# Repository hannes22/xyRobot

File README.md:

# xyRobot

xyRobot is the Framework for my Robot. [Visit my website for more informations](http://xythobuz.org/index.php?p=rob).

## Software used

 + [Peter Fleurys TWI Library](http://homepage.hispeed.ch/peterfleury/avr-software.html)
 + [Linux Version of Peter Danneggers 'fastboot' by H. C. Zimmerer](http://www.mikrocontroller.net/topic/146638)
 + [A Linux compatible Upload Software for fastboot](http://www.avrfreaks.net/index.php?module=Freaks%20Academy&func=viewItem&item_type=project&item_id=1927)

## xyRobotRemote

xyRobotRemote is a Java App which communicates with the Robot Firmware over a serial port. It allows you to shoot pictures with the Gameboy camera and remote-control the robot. It requires Java 6 and could possibly work with Java 7...

## Protocol

The protocol used by the xyRobot Firmware and xyRobotRemote to remote-control the robot is as follows.

<table>
<tr><th>Character Sequence</th><th>Action</th></tr>
<tr><td>ASCII '?'</td><td>Print Firmware Version String</td></tr>
<tr><td>0x80, x</td><td>Rotate the camera Up/Down to the position indicated by the next byte, x, (0 to 180)</td></tr>
<tr><td>0x81, x</td><td>Same as 0x80, but Left/Right</td></tr>
<tr><td>0x82, r1...r8</td><td>Send picture. Camera Register Settings set with the following 8 bytes.</td></tr>
<tr><td>0x83, d, s, dir</td><td>Drive dist cm with speed speed. Direction Forwards if dir = 1, Backwards if dir = 0</td></tr>
<tr><td>0x84, deg, dir</td><td>Rotate deg Degree. Direction Right if dir = 1, ;eft if dir = 0</td></tr>
<tr><td>0x85, r1...r8</td><td>Send picture with 4bit per Pixel.</td></tr>
<tr><td>0x86</td><td>Returns measured distance.</td></tr>
<tr><td>0x87, r1...r8</td><td>Send picture with 2bit per Pixel.</td></tr>
<tr><td>0x88, r1...r8</td><td>Send picture with 1bit per Pixel.</td></tr>
</table>

New major releases could change this protocol or make additions.

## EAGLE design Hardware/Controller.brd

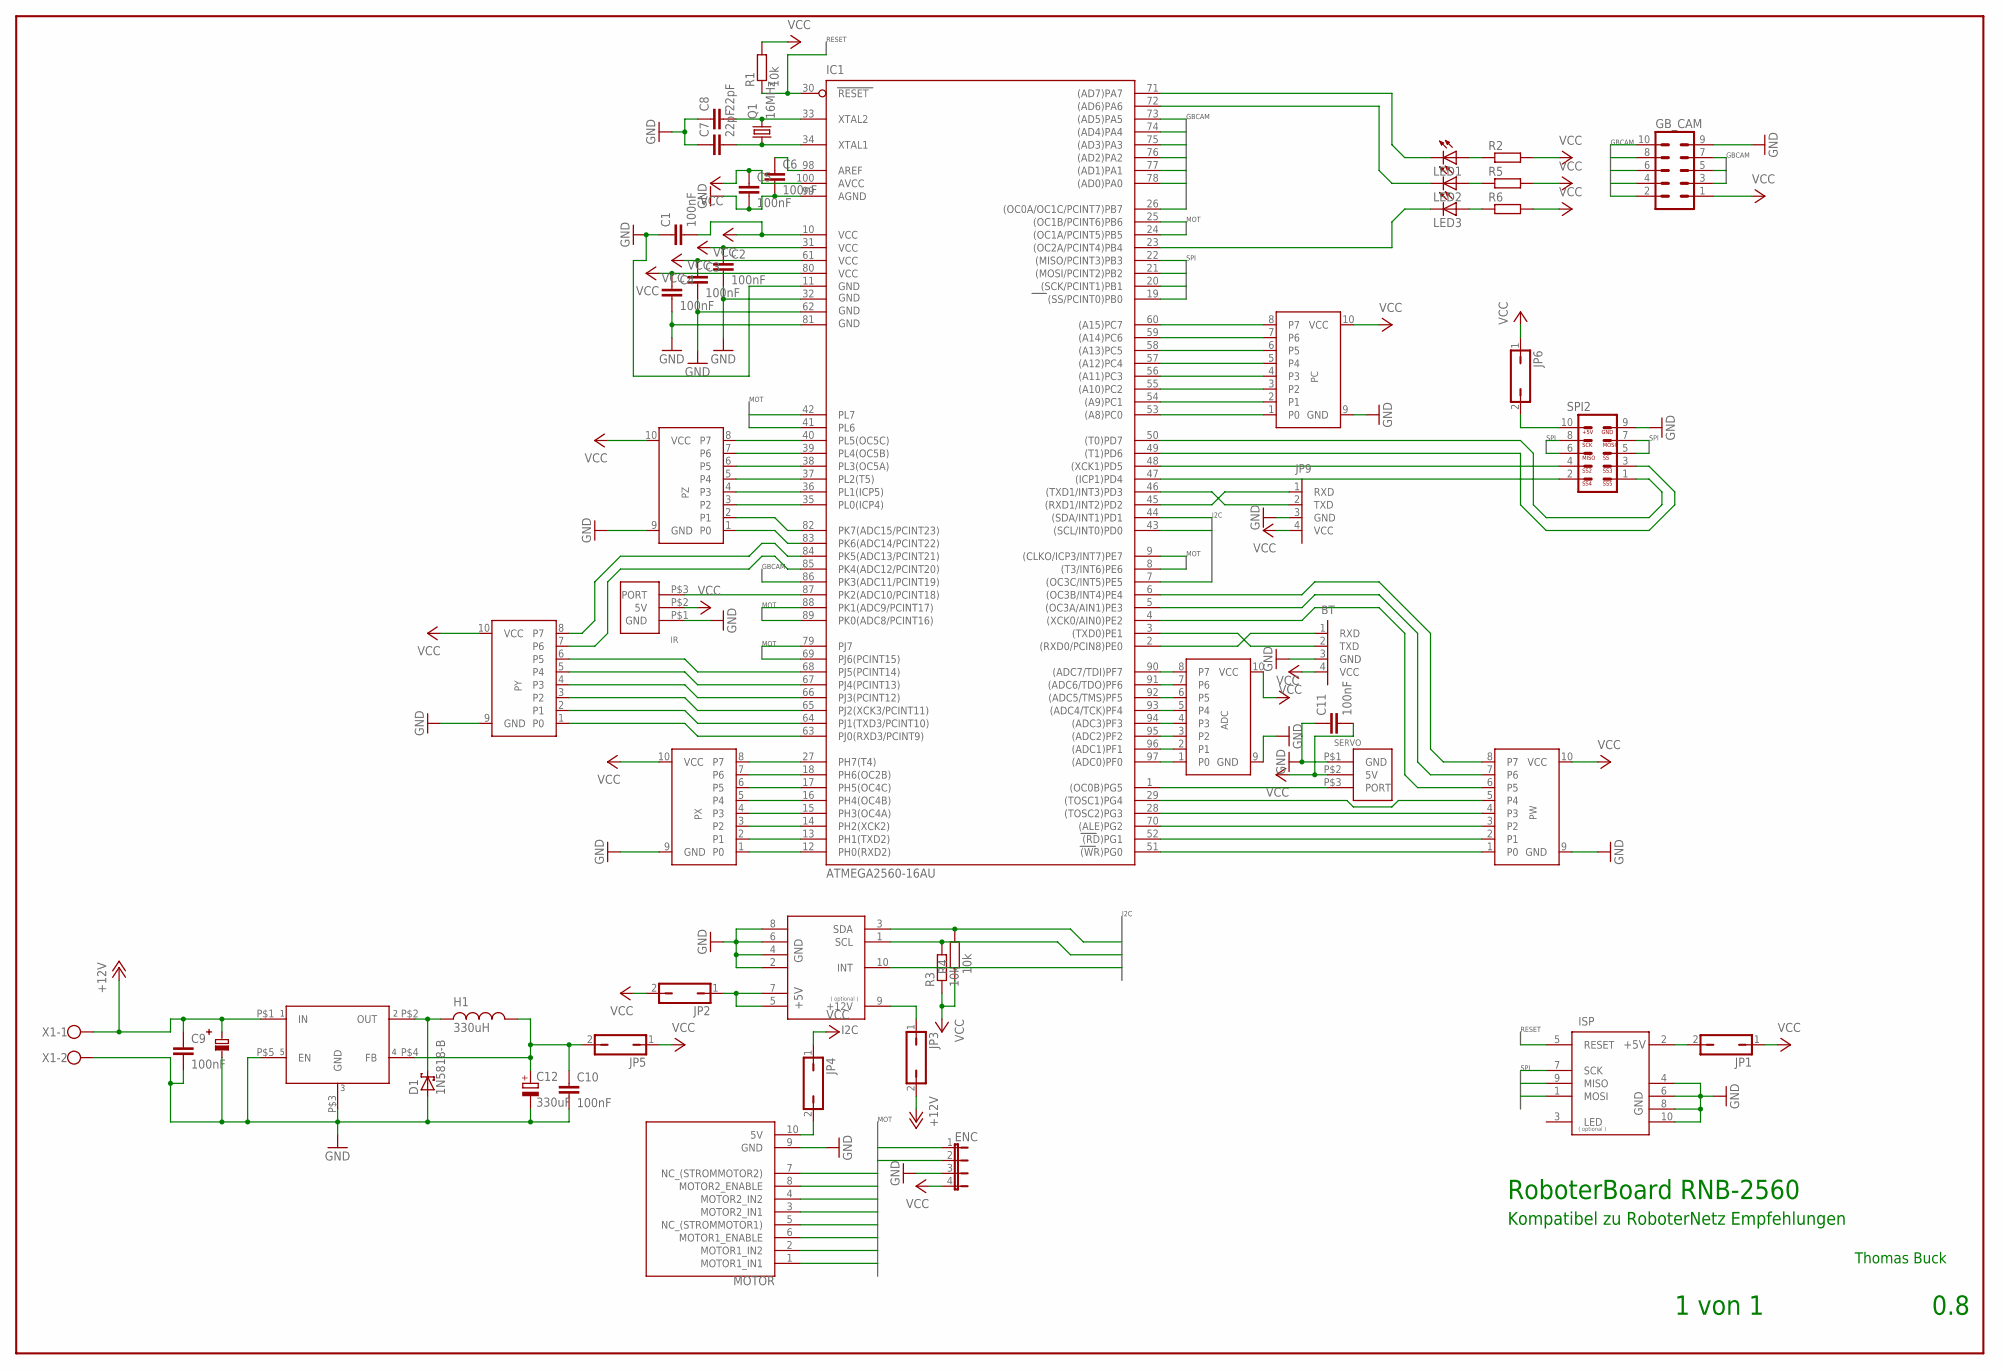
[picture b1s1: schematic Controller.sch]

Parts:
ADC: PORT; ML10
BT: RS232_TTL; 1X04
C1, C2, C3, C4, C5, C6, C9, C10, C11: 100nF; C0603
C7, C8: 22pF; C0603
C12: 330uF; PANASONIC_F
D1: 1N5818-B; DO41-7.6
ENC: JP4E; JP4
GB_CAM: ML10
H1: 330uH; PISR
I2C: I2C; ML10
IC1: ATMEGA2560-16AU; TQFP100
IR: UNIPORT3POL; 1X3SERVO
ISP: AVR-ISP; ML10
JP1, JP2, JP3, JP4, JP5, JP6: JP1Q; JP1
JP9: RS232_TTL; 1X04
LED1, LED2, LED3: LEDCHIP-LED0603; CHIP-LED0603
LM2576-5: LM2576; TO-220
MOTOR: MOTORSTTCKER10POLRNNORM; ML10
PC: PORT; ML10
PW: PORT; ML10
PX: PORT; ML10
PY: PORT; ML10
PZ: PORT; ML10
Q1: 16MHz; HC49/S
R1, R3, R4: 10k; R0603
R2, R5, R6: R-EU_R0603; R0603
SERVO: UNIPORT3POL; 1X3SERVO
SPI2: SPISTECKER; ML10
U$1: 100uF; ELKO_SMD_6.5
X1: W237-102

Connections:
+12V: C9.1, JP3.2, LM2576-5.P$1 (IN), U$1.P$2, X1.1
ANALOG: GB_CAM.8, IC1.86 (PK3(ADC11/PCINT19))
CLK: GB_CAM.6, IC1.77 ((AD1)PA1)
DATA: GB_CAM.3, IC1.74 ((AD4)PA4)
DATASET: GB_CAM.4, IC1.75 ((AD3)PA3)
DREHL: ENC.1, IC1.9 ((CLKO/ICP3/INT7)PE7)
DREHR: ENC.2, IC1.8 ((T3/INT6)PE6)
GND: ADC.9 (GND), BT.3 (GND), C1.1, C2.2, C3.2, C4.2, C5.2, C6.2, C7.1, C8.1, C9.2, C10.2, C11.1, C12.-, D1.A, ENC.3, GB_CAM.9, I2C.2 (GND), I2C.4 (GND), I2C.6 (GND), I2C.8 (GND), IC1.11 (GND), IC1.32 (GND1), IC1.62 (GND2), IC1.81 (GND3), IC1.99 (AGND), IR.P$1 (GND), ISP.4 (GND), ISP.6 (GND), ISP.8 (GND), ISP.10 (GND), JP9.3 (GND), LM2576-5.P$3 (GND), LM2576-5.P$5 (EN), MOTOR.9 (GND), PC.9 (GND), PW.9 (GND), PX.9 (GND), PY.9 (GND), PZ.9 (GND), SERVO.P$1 (GND), SPI2.9, U$1.P$1, X1.2
IN1L: IC1.42 (PL7), MOTOR.1 (MOTOR1_IN1)
IN1R: IC1.79 (PJ7), MOTOR.3 (MOTOR2_IN1)
IN2L: IC1.41 (PL6), MOTOR.2 (MOTOR1_IN2)
IN2R: IC1.69 (PJ6(PCINT15)), MOTOR.4 (MOTOR2_IN2)
INT: I2C.10 (INT), IC1.7 ((OC3C/INT5)PE5)
MISO: IC1.22 ((MISO/PCINT3)PB3), ISP.9 (MISO), SPI2.6
MOSI: IC1.21 ((MOSI/PCINT2)PB2), ISP.1 (MOSI), SPI2.7
unnamed: IC1.87 (PK2(ADC10/PCINT18)), IR.P$3 (PORT)
unnamed: C6.1, IC1.98 (AREF)
unnamed: C8.2, IC1.33 (XTAL2), Q1.2
unnamed: C7.2, IC1.34 (XTAL1), Q1.1
unnamed: IC1.1 ((OC0B)PG5), SERVO.P$3 (PORT)
unnamed: IC1.60 ((A15)PC7), PC.8 (P7)
unnamed: IC1.59 ((A14)PC6), PC.7 (P6)
unnamed: IC1.58 ((A13)PC5), PC.6 (P5)
unnamed: IC1.57 ((A12)PC4), PC.5 (P4)
unnamed: IC1.56 ((A11)PC3), PC.4 (P3)
unnamed: IC1.55 ((A10)PC2), PC.3 (P2)
unnamed: IC1.54 ((A9)PC1), PC.2 (P1)
unnamed: IC1.53 ((A8)PC0), PC.1 (P0)
unnamed: IC1.12 (PH0(RXD2)), PX.1 (P0)
unnamed: IC1.13 (PH1(TXD2)), PX.2 (P1)
unnamed: IC1.14 (PH2(XCK2)), PX.3 (P2)
unnamed: IC1.15 (PH3(OC4A)), PX.4 (P3)
unnamed: IC1.16 (PH4(OC4B)), PX.5 (P4)
unnamed: IC1.17 (PH5(OC4C)), PX.6 (P5)
unnamed: IC1.18 (PH6(OC2B)), PX.7 (P6)
unnamed: IC1.27 (PH7(T4)), PX.8 (P7)
unnamed: IC1.40 (PL5(OC5C)), PZ.8 (P7)
unnamed: IC1.39 (PL4(OC5B)), PZ.7 (P6)
unnamed: IC1.38 (PL3(OC5A)), PZ.6 (P5)
unnamed: IC1.37 (PL2(T5)), PZ.5 (P4)
unnamed: IC1.36 (PL1(ICP5)), PZ.4 (P3)
unnamed: IC1.35 (PL0(ICP4)), PZ.3 (P2)
unnamed: IC1.82 (PK7(ADC15/PCINT23)), PZ.2 (P1)
unnamed: IC1.83 (PK6(ADC14/PCINT22)), PZ.1 (P0)
unnamed: IC1.63 (PJ0(RXD3/PCINT9)), PY.1 (P0)
unnamed: IC1.64 (PJ1(TXD3/PCINT10)), PY.2 (P1)
unnamed: IC1.65 (PJ2(XCK3/PCINT11)), PY.3 (P2)
unnamed: IC1.66 (PJ3(PCINT12)), PY.4 (P3)
unnamed: IC1.67 (PJ4(PCINT13)), PY.5 (P4)
unnamed: IC1.68 (PJ5(PCINT14)), PY.6 (P5)
unnamed: IC1.85 (PK4(ADC12/PCINT20)), PY.7 (P6)
unnamed: IC1.84 (PK5(ADC13/PCINT21)), PY.8 (P7)
unnamed: IC1.51 ((WR)PG0), PW.1 (P0)
unnamed: IC1.52 ((RD)PG1), PW.2 (P1)
unnamed: IC1.70 ((ALE)PG2), PW.3 (P2)
unnamed: IC1.28 ((TOSC2)PG3), PW.4 (P3)
unnamed: IC1.29 ((TOSC1)PG4), PW.5 (P4)
unnamed: IC1.4 ((XCK0/AIN0)PE2), PW.6 (P5)
unnamed: IC1.5 ((OC3A/AIN1)PE3), PW.7 (P6)
unnamed: IC1.6 ((OC3B/INT4)PE4), PW.8 (P7)
unnamed: JP6.2, SPI2.10
unnamed: IC1.47 ((ICP1)PD4), SPI2.2
unnamed: IC1.48 ((XCK1)PD5), SPI2.4
unnamed: IC1.50 ((T0)PD7), SPI2.1
unnamed: IC1.23 ((OC2A/PCINT4)PB4), LED3.C
unnamed: IC1.72 ((AD6)PA6), LED2.C
unnamed: IC1.71 ((AD7)PA7), LED1.C
unnamed: IC1.49 ((T1)PD6), SPI2.3
unnamed: ISP.2 (+5V), JP1.2
unnamed: I2C.5 (+5V), I2C.7 (+5V), JP2.1
unnamed: I2C.9 (+12V), JP3.1
unnamed: JP4.2, MOTOR.10 (5V)
unnamed: ADC.8 (P7), IC1.90 ((ADC7/TDI)PF7)
unnamed: LED1.A, R2.1
unnamed: LED2.A, R5.1
unnamed: LED3.A, R6.1
unnamed: ADC.7 (P6), IC1.91 ((ADC6/TDO)PF6)
unnamed: ADC.6 (P5), IC1.92 ((ADC5/TMS)PF5)
unnamed: D1.C, H1.P$1, LM2576-5.P$2 (OUT)
unnamed: ADC.5 (P4), IC1.93 ((ADC4/TCK)PF4)
unnamed: ADC.4 (P3), IC1.94 ((ADC3)PF3)
unnamed: ADC.3 (P2), IC1.95 ((ADC2)PF2)
unnamed: ADC.2 (P1), IC1.96 ((ADC1)PF1)
unnamed: ADC.1 (P0), IC1.97 ((ADC0)PF0)
unnamed: IC1.46 ((TXD1/INT3)PD3), JP9.2 (TXD)
unnamed: IC1.45 ((RXD1/INT2)PD2), JP9.1 (RXD)
unnamed: C10.1, C12.+, H1.P$2, JP5.2, LM2576-5.P$4 (FB)
PWML: IC1.25 ((OC1B/PCINT6)PB6), MOTOR.6 (MOTOR1_ENABLE)
PWMR: IC1.24 ((OC1A/PCINT5)PB5), MOTOR.8 (MOTOR2_ENABLE)
READIMG: GB_CAM.7, IC1.78 ((AD0)PA0)
RESET: IC1.30 (RESET), ISP.5 (RESET), R1.1
RX: BT.1 (RXD), IC1.2 ((RXD0/PCIN8)PE0)
SCK: IC1.20 ((SCK/PCINT1)PB1), ISP.7 (SCK), SPI2.8
SCL: I2C.1 (SCL), IC1.43 ((SCL/INT0)PD0), R3.2
SDA: I2C.3 (SDA), IC1.44 ((SDA/INT1)PD1), R4.2
SENSL: IC1.88 (PK1(ADC9/PCINT17)), MOTOR.5 (NC_(STROMMOTOR1))
SENSR: IC1.89 (PK0(ADC8/PCINT16)), MOTOR.7 (NC_(STROMMOTOR2))
SERVO: GB_CAM.10, IC1.26 ((OC0A/OC1C/PCINT7)PB7)
SS: IC1.19 ((SS/PCINT0)PB0), SPI2.5
START: GB_CAM.2, IC1.73 ((AD5)PA5)
SYSRES: GB_CAM.5, IC1.76 ((AD2)PA2)
TX: BT.2 (TXD), IC1.3 ((TXD0)PE1)
VCC: ADC.10 (VCC), BT.4 (VCC), C1.2, C2.1, C3.1, C4.1, C5.1, C11.2, ENC.4, GB_CAM.1, IC1.10 (VCC), IC1.31 (VCC1), IC1.61 (VCC2), IC1.80 (VCC3), IC1.100 (AVCC), IR.P$2 (5V), JP1.1, JP2.2, JP4.1, JP5.1, JP6.1, JP9.4 (VCC), PC.10 (VCC), PW.10 (VCC), PX.10 (VCC), PY.10 (VCC), PZ.10 (VCC), R1.2, R2.2, R3.1, R4.1, R5.2, R6.2, SERVO.P$2 (5V)

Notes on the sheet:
RoboterBoard RNB-2560
Thomas Buck
Kompatibel zu RoboterNetz Empfehlungen
0.8
MOT
I2C
SPI
RESET
GBCAM
1 von 1

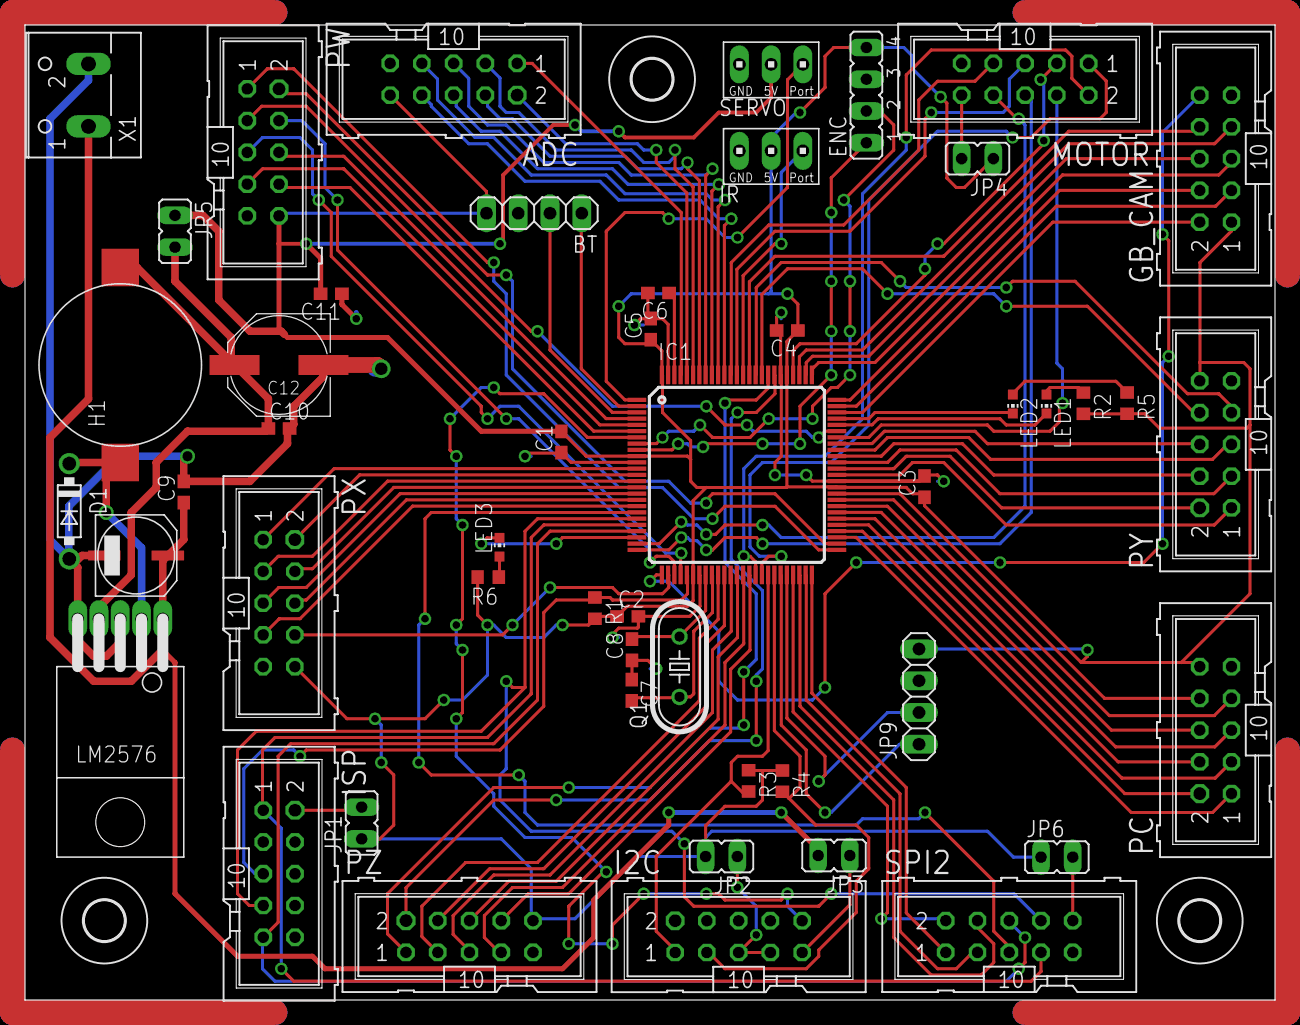
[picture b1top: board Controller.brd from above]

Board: 2 copper layers, 100.0 x 78.0 mm, 53 parts (0 on the bottom side), 103 nets.

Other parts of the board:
U$2, U$3, U$4: 3,2

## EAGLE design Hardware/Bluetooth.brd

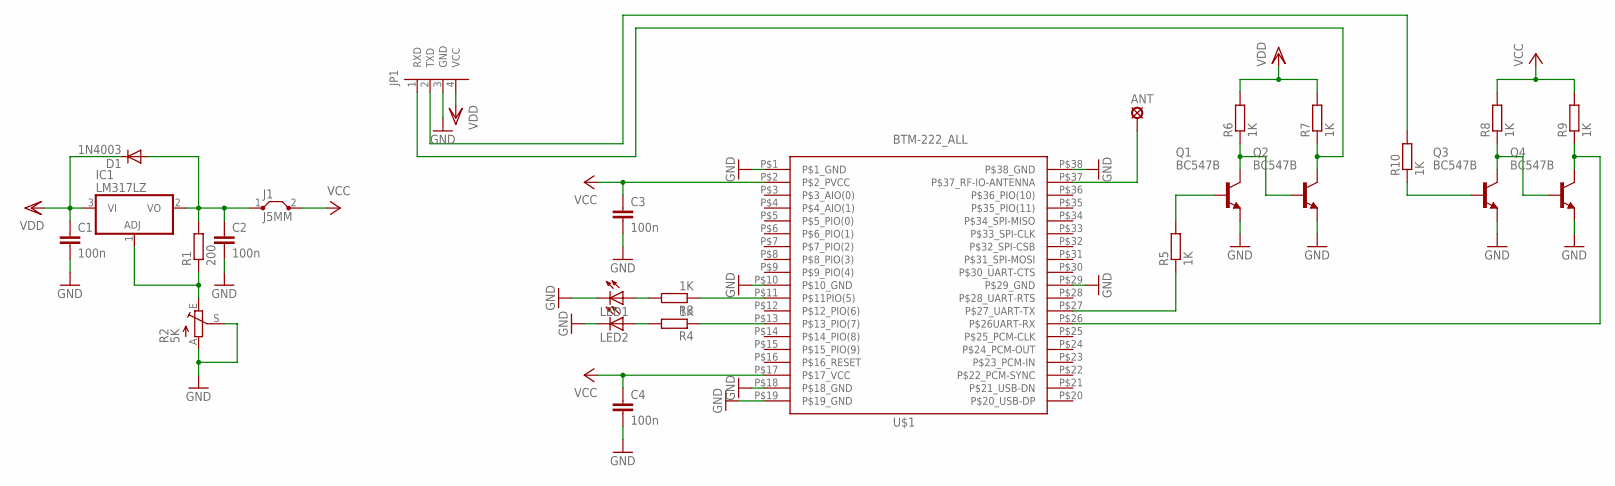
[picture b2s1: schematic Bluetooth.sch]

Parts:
ANT: SE14
C1, C2, C3, C4: 100n; C050-030X075
D1: 1N4003; DO41-10
IC1: LM317LZ; TO92
J1: J5MM; 05
JP1: RS232_TTL; 1X04
LED1, LED2: LED3MM
Q1, Q2, Q3, Q4: BC547B; TO92
R1: 200; 0207/10
R2: 5K; PT-10S
R3, R4, R5, R6, R7, R8, R9, R10: 1K; 0207/10
U$1: BTM-222_ALL; BTM-222

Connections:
GND: C1.2, C2.2, C3.2, C4.2, JP1.3 (GND), LED1.K (C), LED2.K (C), Q1.1 (E), Q2.1 (E), Q3.1 (E), Q4.1 (E), R2.A, R2.S, U$1.P$1 (P$1_GND), U$1.P$10 (P$10_GND), U$1.P$18 (P$18_GND), U$1.P$19 (P$19_GND), U$1.P$29 (P$29_GND), U$1.P$38 (P$38_GND)
unnamed: R3.1, U$1.P$11 (P$11PIO(5))
unnamed: LED1.A, R3.2
unnamed: IC1.1 (ADJ), R1.1, R2.E
unnamed: R4.1, U$1.P$13 (P$13_PIO(7))
unnamed: LED2.A, R4.2
unnamed: Q1.2 (B), R5.2
unnamed: JP1.1 (RXD), Q2.3 (C), R7.1
unnamed: Q1.3 (C), Q2.2 (B), R6.1
unnamed: JP1.2 (TXD), R10.2
unnamed: Q3.2 (B), R10.1
unnamed: R5.1, U$1.P$27 (P$27_UART-TX)
unnamed: Q3.3 (C), Q4.2 (B), R8.1
unnamed: Q4.3 (C), R9.1, U$1.P$26 (P$26UART-RX)
unnamed: ANT.MP, U$1.P$37 (P$37_RF-IO-ANTENNA)
unnamed: C2.1, D1.A, IC1.2 (VO), J1.1, R1.2
VCC: C3.1, C4.1, J1.2, R8.2, R9.2, U$1.P$2 (P$2_PVCC), U$1.P$17 (P$17_VCC)
VDD: C1.1, D1.C, IC1.3 (VI), JP1.4 (VCC), R6.2, R7.2

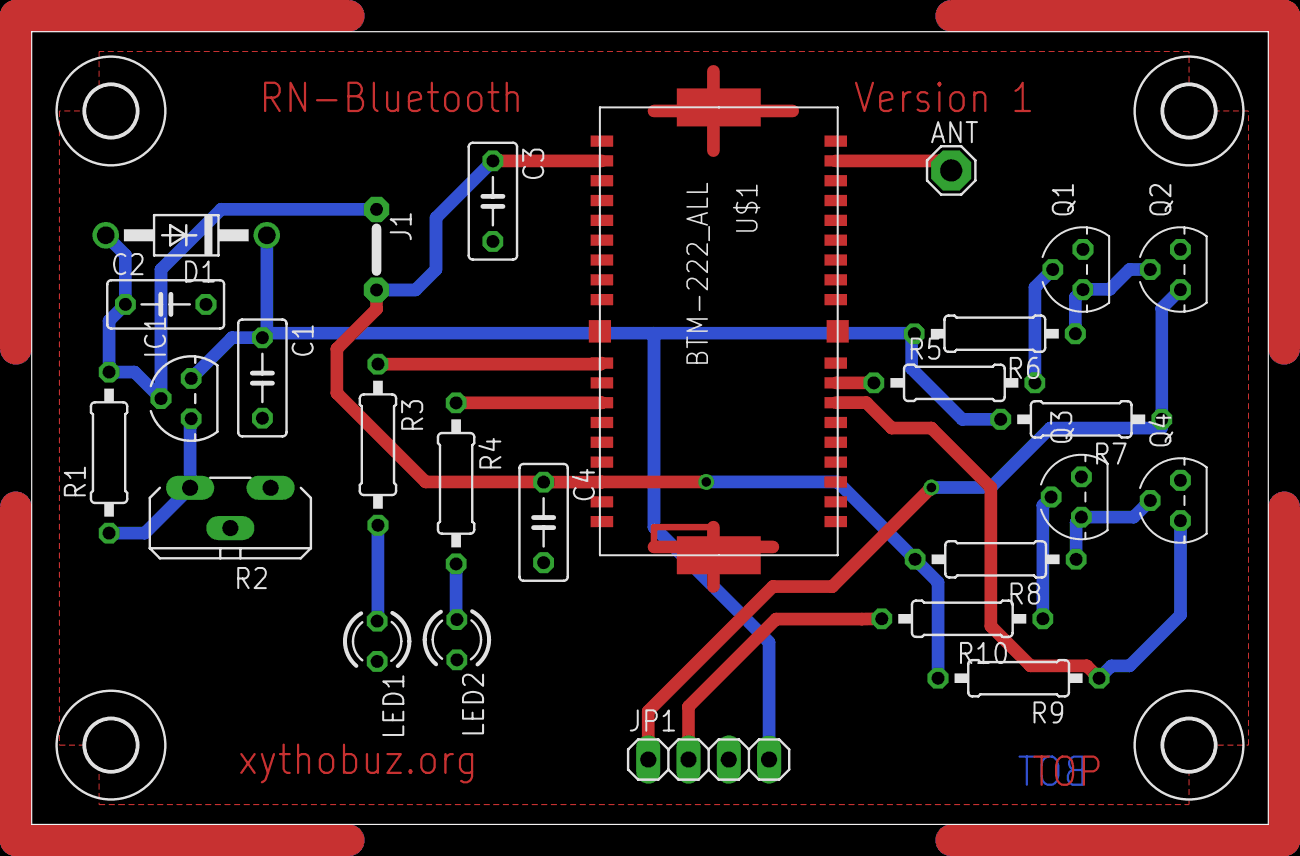
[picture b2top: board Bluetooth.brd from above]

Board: 2 copper layers, 78.0 x 50.0 mm, 30 parts (0 on the bottom side), 18 nets.

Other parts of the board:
U$2, U$3, U$4, U$5: 3,2

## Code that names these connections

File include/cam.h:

/*
 * cam.h
 *
 * Copyright 2011 Thomas Buck <xythobuz@me.com>
 *
 * This file is part of xyRobot.
 *
 * xyRobot is free software: you can redistribute it and/or modify
 * it under the terms of the GNU General Public License as published by
 * the Free Software Foundation, either version 3 of the License, or
 * (at your option) any later version.
 *
 * xyRobot is distributed in the hope that it will be useful,
 * but WITHOUT ANY WARRANTY; without even the implied warranty of
 * MERCHANTABILITY or FITNESS FOR A PARTICULAR PURPOSE.  See the
 * GNU General Public License for more details.
 *
 * You should have received a copy of the GNU General Public License
 * along with xyRobot.  If not, see <http://www.gnu.org/licenses/>.
 */

#ifndef cam_h
#define cam_h

#define CAMPORT PORTA
#define CAMPIN PINA
#define CAMDDR DDRA
#define CAMSTART PA5
#define CAMDATA PA4
#define CAMLOAD PA3
#define CAMRESET PA2
#define CAMCLOCK PA1
#define CAMREAD PA0
#define CAMOUT 11

void camInit(void);
void camStore(uint8_t *regs, uint8_t pos); // Store in memory at (pos * 128 * 128)
void camSendStored(uint8_t pos, uint8_t depth); // Depth in bit/pixel. Possible: 8, 4, 2, 1

#endif

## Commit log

2011-07-30 Added readme, schematics and layout
2011-09-06 Cam spits out data
2011-10-25 GPL notice
2011-10-25 GPL notice 2
2011-10-25 Git problems...
2012-01-01 Menu for driving tests
2012-01-01 Pics are too big for ram...
2012-01-01 removed unused var
2012-01-03 Added servo support
2012-01-03 Added remote
2012-01-03 Fucked up git...
2012-01-03 Added Remote, finally
2012-01-04 Strings in flash. More options in GUI.
2012-02-28 Misc fixes
2012-06-03 Circuit Diagram and Layout are now in EAGLE 6 format.
2012-07-08 Remote now written in Java.
    Also included boot loader in build.
2012-07-08 Hard coded avr6 arch for fast boot. Replaced gawk with awk.
2012-07-09 Worked at Remote.
2012-07-10 Various bug fixes.
2012-07-12 Worked on xyRobotRemote
2012-07-13 Now with serial and lcd menu at the same time.
2012-07-14 Misc work.
2012-07-14 New servo code. More LCD Menu.
2012-07-14 Can now send pics with only 4bit depth.
2012-07-15 Added external SRAM
2012-07-15 Fix mem lib.
2012-07-18 Bugfixes.
2012-07-18 Servos need less cpu time.
2012-07-18 Bigger picture area in remote.
2012-07-18 Added distance view in remote.
2012-07-19 Implemented distance view.
2012-07-21 Extended menu. Fixed Ram.
2012-07-21 Improved low level driving methods.
2012-07-21 Started implementing different color depths.
2012-07-22 Implemented different color depths.
2012-07-22 Removed binaries.
2012-07-23 Misc bugfixes.
2012-07-23 Servo is turned off after reaching position.
2012-07-27 Changed CanvasWindow Behaviour. Now accessed by double click on canvas.
2012-07-27 Changed cam API.
2012-07-28 ADC now with better offset voltage.
    Also included utility to test canvas with different pics.
2012-07-28 Restructured camera code.
2012-07-28 Easier flashing with auto reset.
2012-07-29 Improved Remote.
2012-07-29 Included "splash screen" for remote.
2012-07-29 Integrated ImageTest.
2012-07-29 Extended readme.
2012-07-30 Register Dialog slightly resizable.
2012-07-30 Registers resizeable.
2012-07-30 Started making main window resizable.
2012-07-31 Fixed libSerial makefile for linux.
2012-08-01 Fixed libSerial for linux with glibc.
2012-08-01 Removed whitespace
2012-08-02 Fixed remote bugs.
2012-08-02 Reordered methods in Remote.java
2012-08-03 Removed warnings in Java 7.
2012-08-03 Warnings in Java 7 are back. Ensures compatibility with Java 6.
2012-08-03 Made remote window resizable.
2012-08-04 Added mac app bundling.
2012-08-04 Moved mac bundle.
2012-08-04 Fixed mac app.
2012-08-06 First major release.
2012-08-07 Moved handlers into own file.
2012-08-07 Implemented simple task scheduler.
2012-08-07 Added some watchdog resets.
2012-08-07 Added timed task scheduling.
2012-08-07 Scheduler keeps statistics.
2012-08-07 Watchdog reset now in own task…
2012-08-08 Changed task statistics.
2012-08-08 Changed statistics again.
2012-08-10 Explained task managing
2012-08-28 Memory Error Check considerably faster.
2012-08-30 App Bundling not compatible with Mountain Lion!
